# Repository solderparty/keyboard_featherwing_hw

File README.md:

# The Keyboard FeatherWing (Rev 2)

The Keyboard FeatherWing is an easy way to add a handheld Qwerty keyboard and a 2.6 color display (+ more) to your project! It fits well in your hands and is great for typing with your thumbs, early 2000s-style.

The FeatherWing itself does not contain an MCU/CPU/SoC that you can program; you will need a board compatible with the [Adafruit Feather System](https://learn.adafruit.com/adafruit-feather/feather-specification).

For revision 1, see the tag `rev1`.

# Technical details
- 2.6 320x240 16-bit color LCD with resistive touch screen
- QWERTY keyboard
- 5-way button
- 4 soft tactile buttons
- A Neopixel
- microSD connector
- Stemma QT/Qwiic connector
- An Ambient Light Sensor
- On/Off switch
- Dual row sockets
- Four mounting holes
- GPIO solder jumpers

# Links

For more information visit https://kfw.solder.party/

You can find example code here: https://github.com/solderparty/keyboard_featherwing_sw

This board uses an ATSAMD20 chip as a i2c peripheral that can be polled to get the key FIFO, as well as used as a simple GPIO Expander, the firmware for the SAM can be found here: https://github.com/solderparty/bbq10kbd_i2c_sw

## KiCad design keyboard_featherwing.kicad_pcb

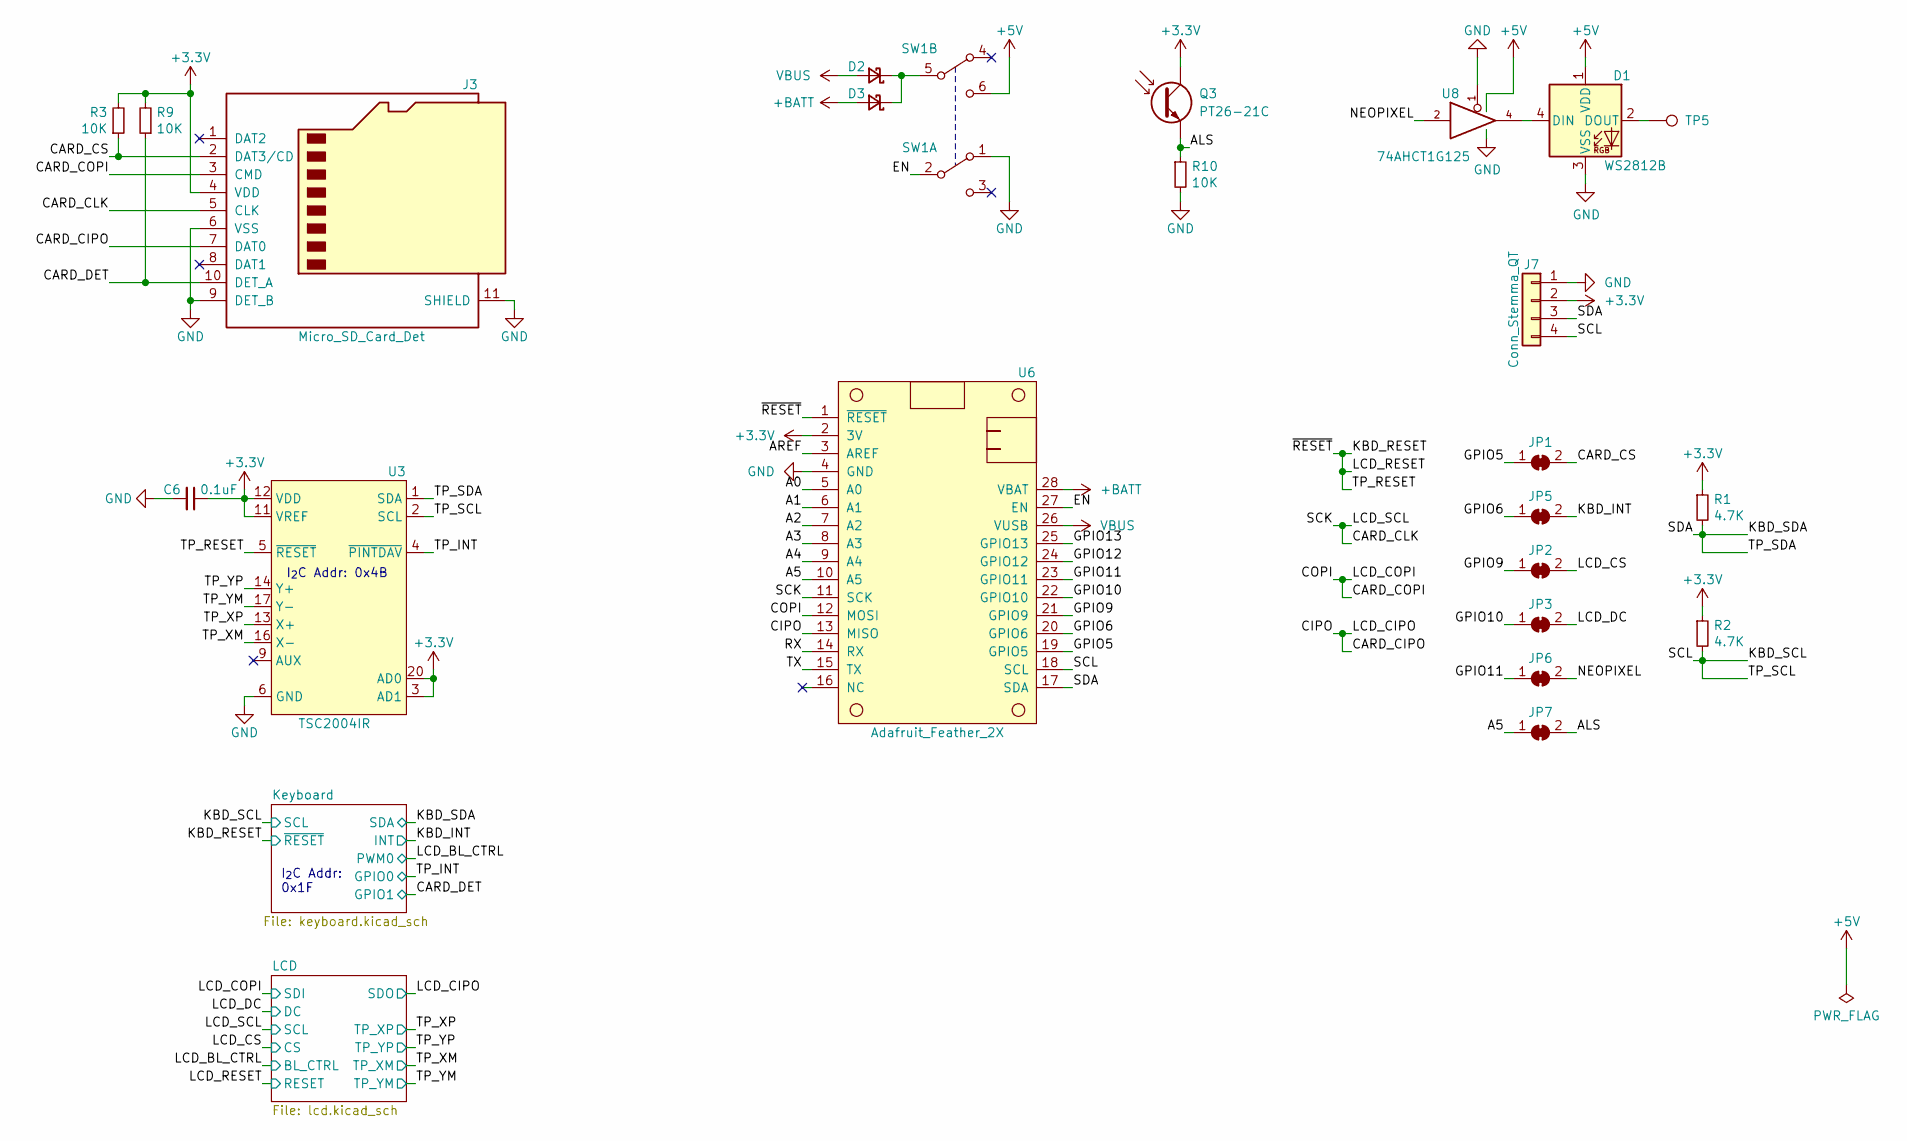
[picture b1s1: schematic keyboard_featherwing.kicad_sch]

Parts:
C6: 0.1uF; C_0603_1608Metric
D1: WS2812B; LED_WS2812B_PLCC4_5.0x5.0mm_P3.2mm; LCSC C11458
D2, D3: S1JHE; D_SOD-323_HandSoldering; LCSC C114023
J3: Micro_SD_Card_Det; microSD_HC_Molex_104031-0811
J7: Conn_Stemma_QT; JST_SH_SM04B-SRSS-TB_1x04-1MP_P1.00mm_Horizontal; LCSC C145956
JP1: SB_CARD_CS; SolderJumper-2_P1.3mm_Bridged_RoundedPad1.0x1.5mm
JP2: SB_LCD_CS; SolderJumper-2_P1.3mm_Bridged_RoundedPad1.0x1.5mm
JP3: SB_LCD_DC; SolderJumper-2_P1.3mm_Bridged_RoundedPad1.0x1.5mm
JP5: SB_KBD_INT; SolderJumper-2_P1.3mm_Bridged_RoundedPad1.0x1.5mm
JP6: SB_NEOPIXEL; SolderJumper-2_P1.3mm_Bridged_RoundedPad1.0x1.5mm
JP7: SB_ALS; SolderJumper-2_P1.3mm_Bridged_RoundedPad1.0x1.5mm
Q3: PT26-21C; Everlight_PT26-21C
R1, R2: 4.7K; R_0603_1608Metric
R3, R9, R10: 10K; R_0603_1608Metric
SW1: SK-3245S-Lx-B; K3-x245S
TP5: TP_NEOPIXEL_OUT; TestPoint_Pad_D2.0mm
U3: TSC2004IR; QFN-20-1EP_4x4mm_P0.5mm_EP2.7x2.7mm; LCSC C128424
U6: Adafruit_Feather_2X; FeatherWing
U8: 74AHCT1G125; SOT-353_SC-70-5; LCSC C151890

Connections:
+3V3: C6.1, J3.4 (VDD), J7.2, Q3.1, Q3.3, R1.1, R2.1, R3.2, R9.2, U3.3 (AD1), U3.7 (VDD), U3.11 (VREF), U3.12 (VDD), U3.20 (AD0), U6.2 (3V); also elsewhere on the board
+5V: D1.1 (VDD), SW1.6 (C), U8.5 (VCC)
+BATT: D3.2 (A), U6.28 (VBAT)
/A0: U6.5 (A0)
/A1: U6.6 (A1)
/A2: U6.7 (A2)
/A3: U6.8 (A3)
/A4: U6.9 (A4)
/A5: JP7.1 (A), U6.10 (A5)
/ALS: JP7.2 (B), Q3.2, Q3.4, R10.1
/AREF: U6.3 (AREF)
/CARD_CIPO: J3.7 (DAT0), U6.13 (MISO); also elsewhere on the board
/CARD_CLK: J3.5 (CLK), U6.11 (SCK); also elsewhere on the board
/CARD_COPI: J3.3 (CMD), U6.12 (MOSI); also elsewhere on the board
/CARD_CS: J3.2 (DAT3/CD), JP1.2 (B), R3.1
/CARD_DET: J3.10 (DET_A), R9.1; also elsewhere on the board
/EN: SW1.2 (B), U6.27 (EN)
/GPIO5: JP1.1 (A), U6.19 (GPIO5)
/GPIO6: JP5.1 (A), U6.20 (GPIO6)
/GPIO9: JP2.1 (A), U6.21 (GPIO9)
/GPIO10: JP3.1 (A), U6.22 (GPIO10)
/GPIO11: JP6.1 (A), U6.23 (GPIO11)
/GPIO12: U6.24 (GPIO12)
/GPIO13: U6.25 (GPIO13)
/KBD_INT: JP5.2 (B); also elsewhere on the board
/KBD_RESET: U3.5 (~RESET~), U6.1 (~RESET~); also elsewhere on the board
/KBD_SCL: J7.4, R2.2, U3.2 (SCL), U6.18 (SCL); also elsewhere on the board
/KBD_SDA: J7.3, R1.2, U3.1 (SDA), U6.17 (SDA); also elsewhere on the board
/LCD_CS: JP2.2 (B); also elsewhere on the board
/LCD_DC: JP3.2 (B); also elsewhere on the board
/NEOPIXEL: JP6.2 (B), U8.2
/RX: U6.14 (RX)
/TP_INT: U3.4 (~PINTDAV~); also elsewhere on the board
/TP_XM: U3.16 (X-); also elsewhere on the board
/TP_XP: U3.13 (X+); also elsewhere on the board
/TP_YM: U3.17 (Y-); also elsewhere on the board
/TP_YP: U3.14 (Y+); also elsewhere on the board
/TX: U6.15 (TX)
GND: C6.2, D1.3 (VSS), J3.6 (VSS), J3.9 (DET_B), J3.11 (SHIELD), J7.1, R10.2, SW1.1 (A), U3.6 (GND), U3.10 (GND), U3.15 (GND), U3.18 (GND), U3.21 (GND), U6.4 (GND), U8.1, U8.3 (GND); also elsewhere on the board
unnamed: D1.2 (DOUT), TP5.1
unnamed: D1.4 (DIN), U8.4
unnamed: D2.1 (K), D3.1 (K), SW1.5 (B)
VBUS: D2.2 (A), U6.26 (VUSB)

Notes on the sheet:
I_{2}C Addr: 0x1F
I_{2}C Addr: 0x4B

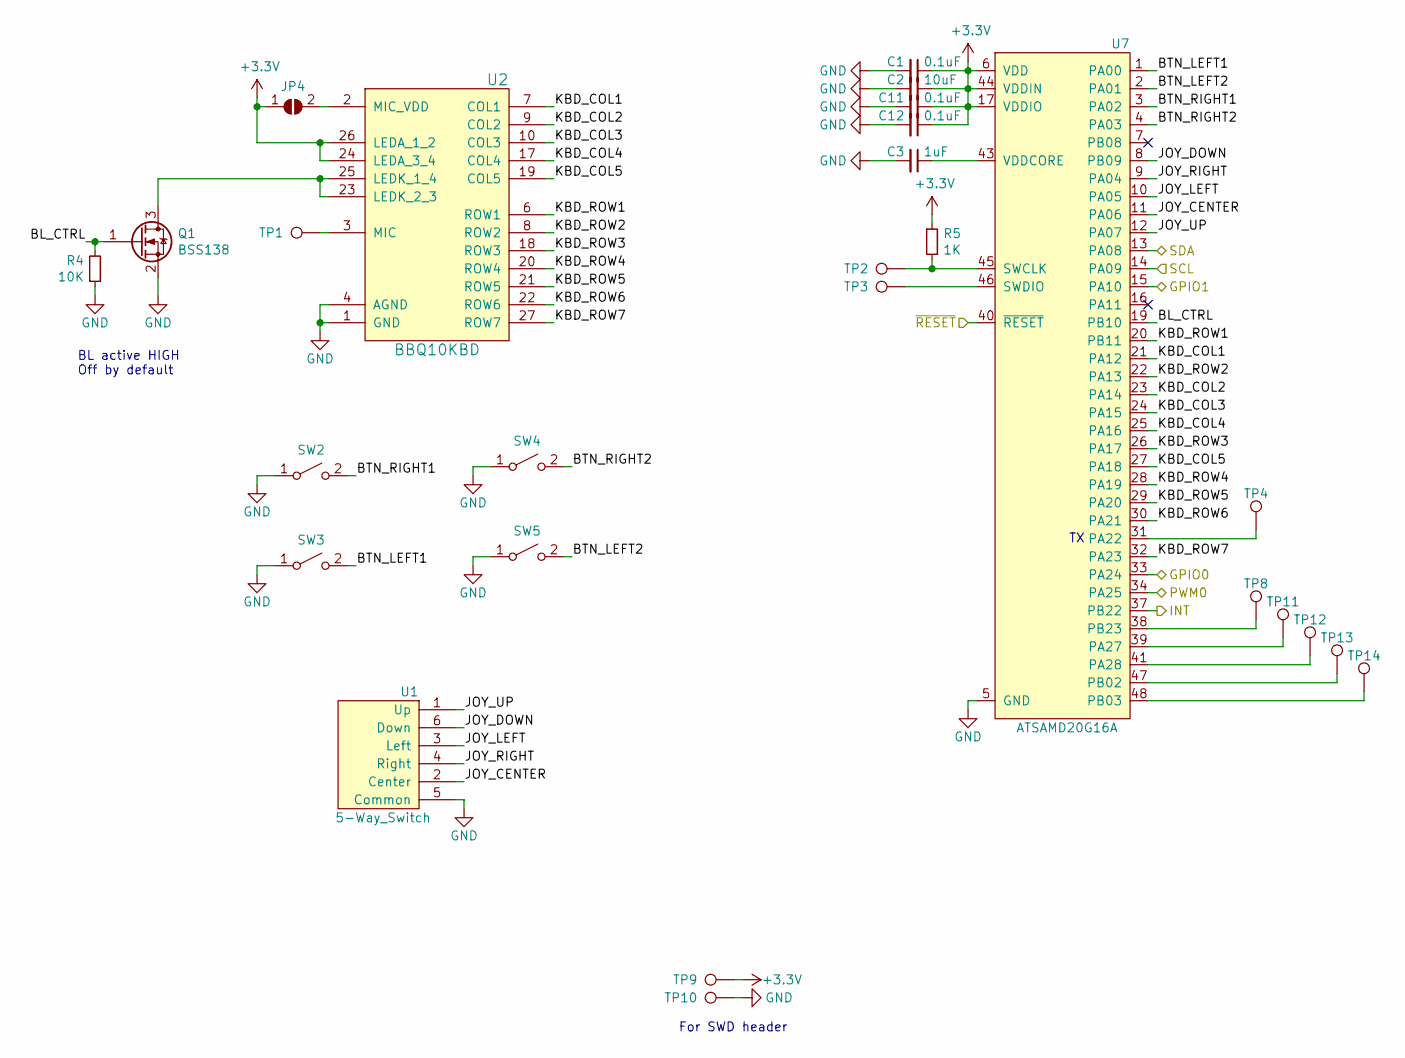
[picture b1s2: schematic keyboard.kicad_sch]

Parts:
C1, C11, C12: 0.1uF; C_0603_1608Metric
C2: 10uF; C_0603_1608Metric
C3: 1uF; C_0603_1608Metric
JP4: SB_MIC_VDD; SolderJumper-2_P1.3mm_Open_RoundedPad1.0x1.5mm
Q1: BSS138; SOT-23; LCSC C112239
R4: 10K; R_0603_1608Metric
R5: 1K; R_0603_1608Metric
SW2: SW_RIGHT1; RMT-CZ66
SW3: SW_LEFT1; RMT-CZ66
SW4: SW_RIGHT2; RMT-CZ66
SW5: SW_LEFT2; RMT-CZ66
TP1: TP_MIC; TestPoint_Pad_D2.0mm
TP2: TP_KBD_SWCLK; TestPoint_Pad_D2.0mm
TP3: TP_KBD_SWDIO; TestPoint_Pad_D2.0mm
TP4: TP_KBD_TX; TestPoint_Pad_D2.0mm
TP8: TP_GPIO2; TestPoint_Pad_D2.0mm
TP9: TP_KBD_3V; TestPoint_Pad_D2.0mm
TP10: TP_KBD_GND; TestPoint_Pad_D2.0mm
TP11: TP_GPIO3; TestPoint_Pad_D2.0mm
TP12: TP_GPIO4; TestPoint_Pad_D2.0mm
TP13: TP_GPIO5; TestPoint_Pad_D2.0mm
TP14: TP_GPIO6; TestPoint_Pad_D2.0mm
U1: 5-Way_Switch; SF303GJ26
U2: BBQ10KBD; BM14B(0.8)-24DS-0.4V(53)
U7: ATSAMD20G16A; QFN-48-1EP_7x7mm_P0.5mm_EP5.15x5.15mm

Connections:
+3V3: C1.1, C2.1, C11.1, C12.1, JP4.1 (A), R5.1, TP9.1, U2.24 (LEDA_3_4), U2.26 (LEDA_1_2), U7.6 (VDD), U7.17 (VDDIO), U7.36 (VDDIO), U7.44 (VDDIN); also elsewhere on the board
/CARD_DET: U7.15 (PA10); also elsewhere on the board
/KBD_INT: U7.37 (PB22); also elsewhere on the board
/KBD_RESET: U7.40 (~RESET~); also elsewhere on the board
/KBD_SCL: U7.14 (PA09); also elsewhere on the board
/KBD_SDA: U7.13 (PA08); also elsewhere on the board
/Keyboard/BL_CTRL: Q1.1 (G), R4.2, U7.19 (PB10)
/Keyboard/BTN_LEFT1: SW3.2 (B), U7.1 (PA00)
/Keyboard/BTN_LEFT2: SW5.2 (B), U7.2 (PA01)
/Keyboard/BTN_RIGHT1: SW2.2 (B), U7.3 (PA02)
/Keyboard/BTN_RIGHT2: SW4.2 (B), U7.4 (PA03)
/Keyboard/JOY_CENTER: U1.2 (Center), U7.11 (PA06)
/Keyboard/JOY_DOWN: U1.6 (Down), U7.8 (PB09)
/Keyboard/JOY_LEFT: U1.3 (Left), U7.10 (PA05)
/Keyboard/JOY_RIGHT: U1.4 (Right), U7.9 (PA04)
/Keyboard/JOY_UP: U1.1 (Up), U7.12 (PA07)
/Keyboard/KBD_COL1: U2.7 (COL1), U7.21 (PA12)
/Keyboard/KBD_COL2: U2.9 (COL2), U7.23 (PA14)
/Keyboard/KBD_COL3: U2.10 (COL3), U7.24 (PA15)
/Keyboard/KBD_COL4: U2.17 (COL4), U7.25 (PA16)
/Keyboard/KBD_COL5: U2.19 (COL5), U7.27 (PA18)
/Keyboard/KBD_ROW1: U2.6 (ROW1), U7.20 (PB11)
/Keyboard/KBD_ROW2: U2.8 (ROW2), U7.22 (PA13)
/Keyboard/KBD_ROW3: U2.18 (ROW3), U7.26 (PA17)
/Keyboard/KBD_ROW4: U2.20 (ROW4), U7.28 (PA19)
/Keyboard/KBD_ROW5: U2.21 (ROW5), U7.29 (PA20)
/Keyboard/KBD_ROW6: U2.22 (ROW6), U7.30 (PA21)
/Keyboard/KBD_ROW7: U2.27 (ROW7), U7.32 (PA23)
/LCD_BL_CTRL: U7.34 (PA25); also elsewhere on the board
/TP_INT: U7.33 (PA24); also elsewhere on the board
GND: C1.2, C2.2, C3.2, C11.2, C12.2, Q1.2 (S), R4.1, SW2.1 (A), SW3.1 (A), SW4.1 (A), SW5.1 (A), TP10.1, U1.5 (Common), U1.SHIELD, U2.1 (GND), U2.4 (AGND), U2.5 (GND), U2.11 (GND), U2.12 (GND), U2.13 (GND), U2.14 (GND), U2.15 (GND), U2.16 (GND), U2.28 (GND), U7.5 (GND), U7.18 (GND), U7.35 (GND), U7.42 (GND); also elsewhere on the board
unnamed: C3.1, U7.43 (VDDCORE)
unnamed: JP4.2 (B), U2.2 (MIC_VDD)
unnamed: Q1.3 (D), U2.23 (LEDK_2_3), U2.25 (LEDK_1_4)
unnamed: R5.2, TP2.1, U7.45 (SWCLK)
unnamed: TP1.1, U2.3 (MIC)
unnamed: TP3.1, U7.46 (SWDIO)
unnamed: TP4.1, U7.31 (PA22)
unnamed: TP8.1, U7.38 (PB23)
unnamed: TP11.1, U7.39 (PA27)
unnamed: TP12.1, U7.41 (PA28)
unnamed: TP13.1, U7.47 (PB02)
unnamed: TP14.1, U7.48 (PB03)

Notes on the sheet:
BL active HIGH Off by default
For SWD header

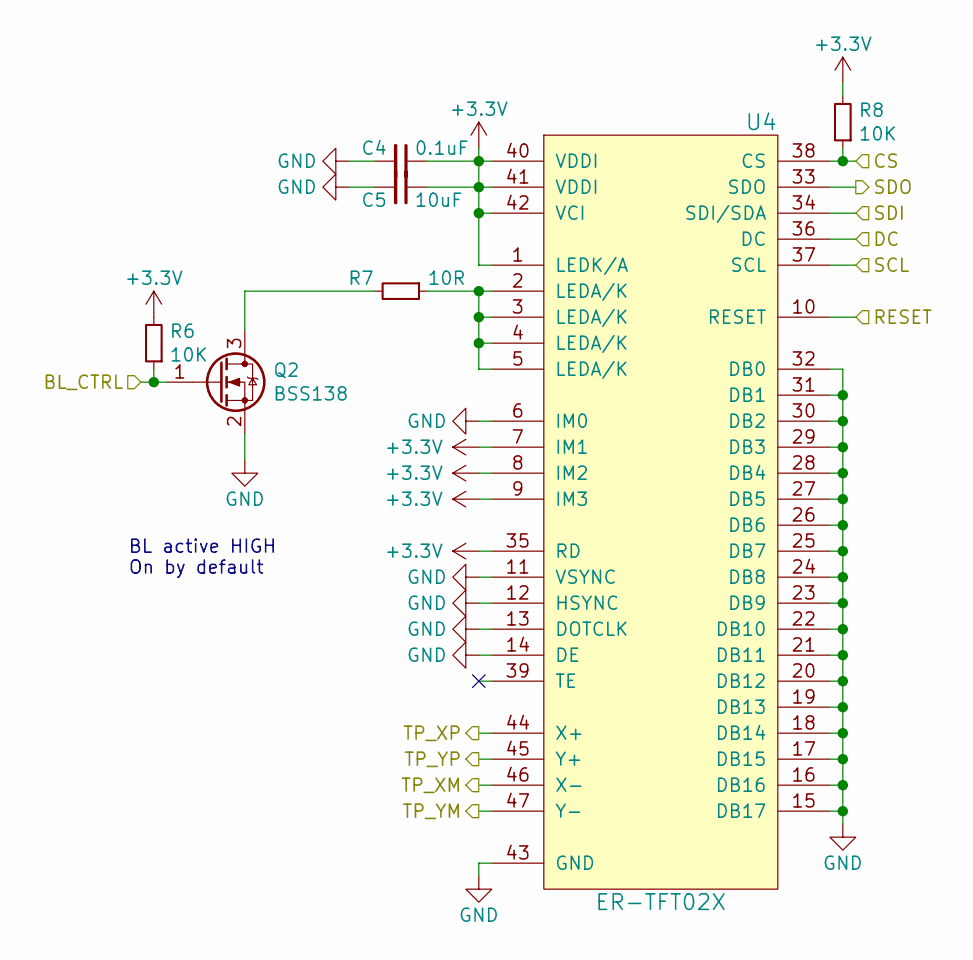
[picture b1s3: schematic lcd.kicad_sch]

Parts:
C4: 0.1uF; C_0603_1608Metric
C5: 10uF; C_0603_1608Metric
Q2: BSS138; SOT-23; LCSC C112239
R6, R8: 10K; R_0603_1608Metric
R7: 10R; R_0603_1608Metric
U4: ER-TFT02X; ER-CON50HT-1

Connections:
+3V3: C4.1, C5.1, R6.2, R8.2, U4.1 (LEDK/A), U4.7 (IM1), U4.8 (IM2), U4.9 (IM3), U4.35 (RD), U4.40 (VDDI), U4.41 (VDDI), U4.42 (VCI); also elsewhere on the board
/CARD_CIPO: U4.33 (SDO); also elsewhere on the board
/CARD_CLK: U4.37 (SCL); also elsewhere on the board
/CARD_COPI: U4.34 (SDI/SDA); also elsewhere on the board
/KBD_RESET: U4.10 (RESET); also elsewhere on the board
/LCD_BL_CTRL: Q2.1 (G), R6.1; also elsewhere on the board
/LCD_CS: R8.1, U4.38 (CS); also elsewhere on the board
/LCD_DC: U4.36 (DC); also elsewhere on the board
/TP_XM: U4.46 (X-); also elsewhere on the board
/TP_XP: U4.44 (X+); also elsewhere on the board
/TP_YM: U4.47 (Y-); also elsewhere on the board
/TP_YP: U4.45 (Y+); also elsewhere on the board
GND: C4.2, C5.2, Q2.2 (S), U4.6 (IM0), U4.11 (VSYNC), U4.12 (HSYNC), U4.13 (DOTCLK), U4.14 (DE), U4.15 (DB17), U4.16 (DB16), U4.17 (DB15), U4.18 (DB14), U4.19 (DB13), U4.20 (DB12), U4.21 (DB11), U4.22 (DB10), U4.23 (DB9), U4.24 (DB8), U4.25 (DB7), U4.26 (DB6), U4.27 (DB5), U4.28 (DB4), U4.29 (DB3), U4.30 (DB2), U4.31 (DB1), U4.32 (DB0), U4.43 (GND), U4.48 (GND), U4.49 (GND), U4.50 (GND); also elsewhere on the board
unnamed: Q2.3 (D), R7.2
unnamed: R7.1, U4.2 (LEDA/K), U4.3 (LEDA/K), U4.4 (LEDA/K), U4.5 (LEDA/K)

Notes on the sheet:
BL active HIGH On by default

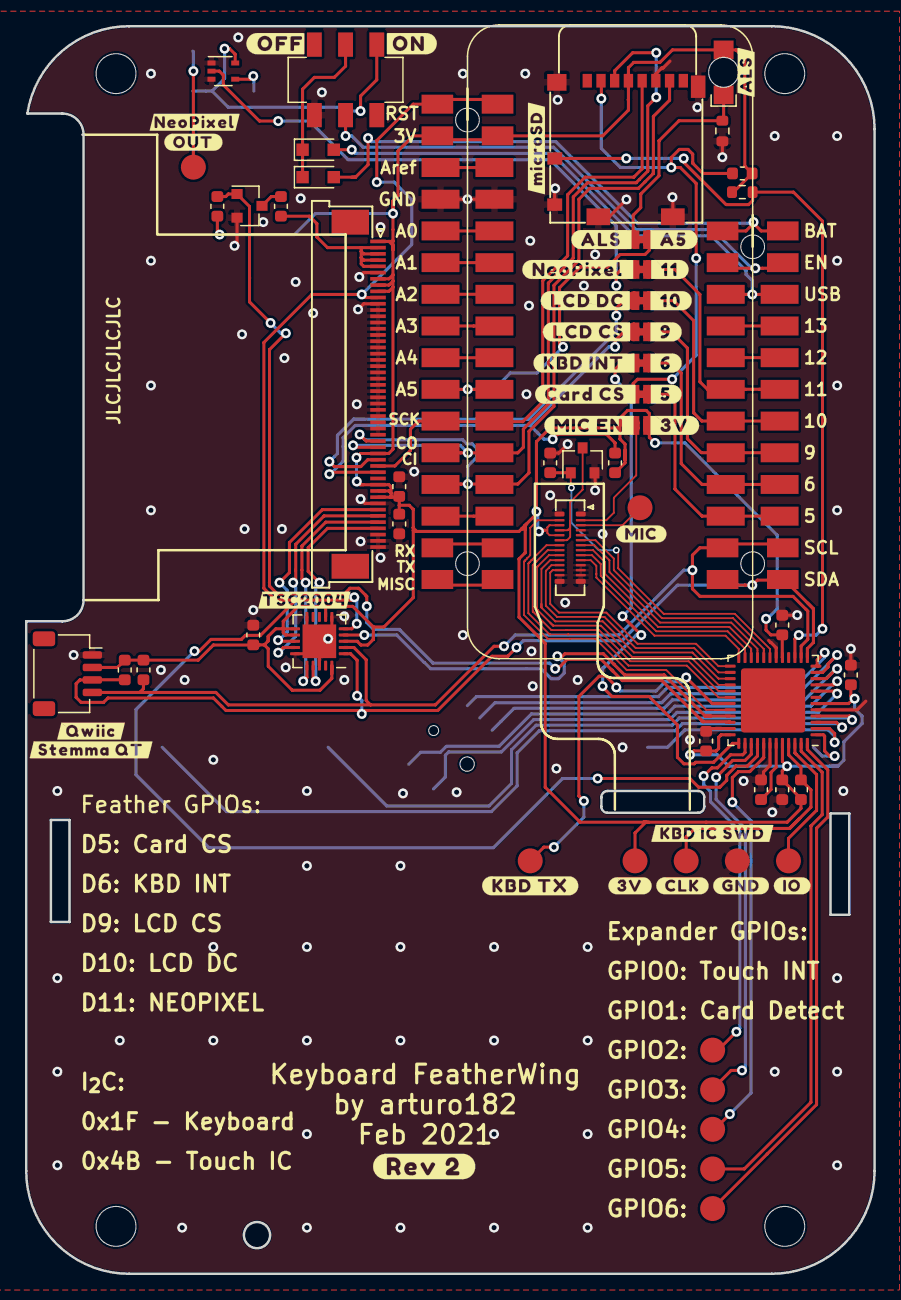
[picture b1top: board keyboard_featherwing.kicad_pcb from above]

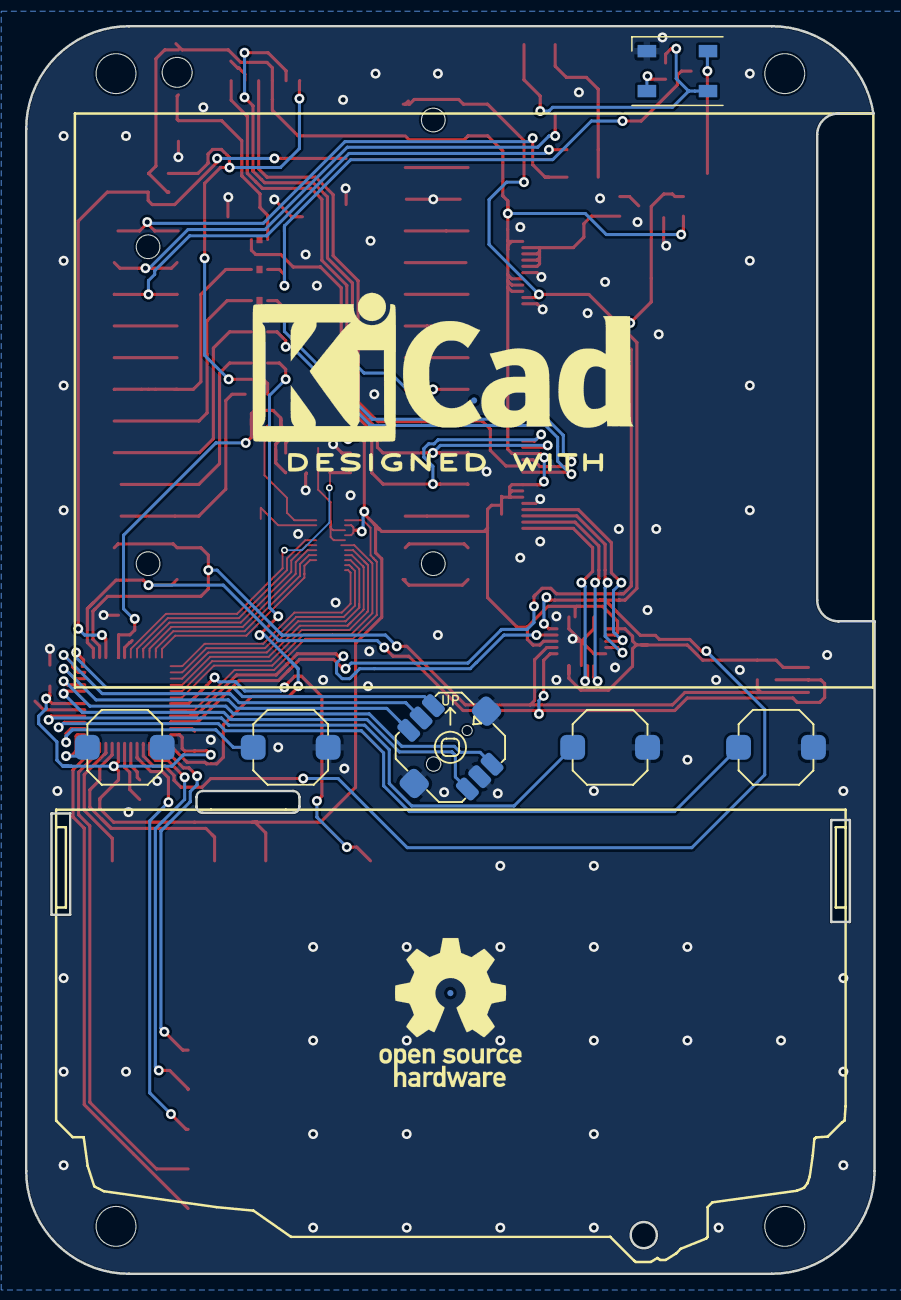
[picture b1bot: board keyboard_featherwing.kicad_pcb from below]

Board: 2 copper layers, 68.0 x 100.0 mm, 57 parts (6 on the bottom side), 70 nets.

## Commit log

2021-06-28 Production HW Rev 2
